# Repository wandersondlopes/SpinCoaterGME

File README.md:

# SpinCoaterGME

Nesse repositorio encontra-se todos as informações de projeto para se construir um Spin Coater Homemade. Um Spin Coater é um equipamento muito utilzado em laboratórios. Utilizando esse equipamento podemos produzir filmes de varias espessuras de acordo com o procedimento experimental. Esse equipamento foi criado no GME (Grupo de Métodos Eletroforéticos/UFG - Brasil) e sua utilização era principalmente para produção de filmes poliméricos de PDMS, PMMA e resinas. 

Esse sistema utiliza um sistema embarcado com firmware que tem código escrito em C++ e um aplicativo para dispositivos Android que possuam bluetooth. Foi entendido que era necessario muita praticidade e facilidade no manuseio das amostras. Então concebemos um dispositivo de fácil utilização via bluetooth. Com isso podemos facilitar o procedimento experimental e aumentar a produtividade nesse dispositivo.

# Aplicativo

O aplicativo mobile foi desenvolvido na plataforma Mit App Inventor e utiliza a comunicação via bluetooth para troca de dados. A interface do aplicativo tem as configurações disponiveis para realizar o procedimento experimental. O usuário pode escrever a intensidade de rotação e o tempo de rotação em segundos. Foi concebida também uma tela de login para que o usuário possa conectar seu dispositivo e configurar a senha de acesso ao aplicativo.

# Senhas de acesso

Existem duas senhas padrão a serem configuradas para o funcionamento spin coater.
A senha do aplicativo mobile e módulo HC-06. Atualmente a maneira de acessar o aplicativo com um usuário tem as seguintes etapas: precione "Entrar" com toque longo, apos aparecer a notificação para entrar como administrador confirme "Sim". A senha do módulo HC-06 é configurada por padrão "1234" e é utilizada para conectar o celular ao módulo.

# SpinCoaterV3 AT-AU - Sistema Embarcado

O Sistema Embarcado do Spin Coater foi feito utilizando Eagle, está também disponível um pdf com o fotolito para confecção da PCB. Nesse diretório encontra-se todos os arquivos para a confecção do hardware do spin coater. Foram deixadas disponíveis os terminais responsáveis dedicados para a gravação do código em hexadecimal (.hex) no microcontrolador ATmega328au.

Video de demontração:
https://youtu.be/IxnT_PpbAdY

# Firmware

O firmware foi escrito em liguagem C++ para Arduino. Para que se possa controlar a velocidade de rotação do motor determinamos o duty cicle do sinal fornecido ao driver do motor. Dessa maneira conseguimos determinar o fornecimento de corrente para o motor e sua velocidade. Como o microcontrolador opera como um oscilador nessa etapa utilizamos o dispositivo mobile para servir como timer e determinar o tempo do procedimento de rotação.

O Sistema desenvolvido é OpenSource.

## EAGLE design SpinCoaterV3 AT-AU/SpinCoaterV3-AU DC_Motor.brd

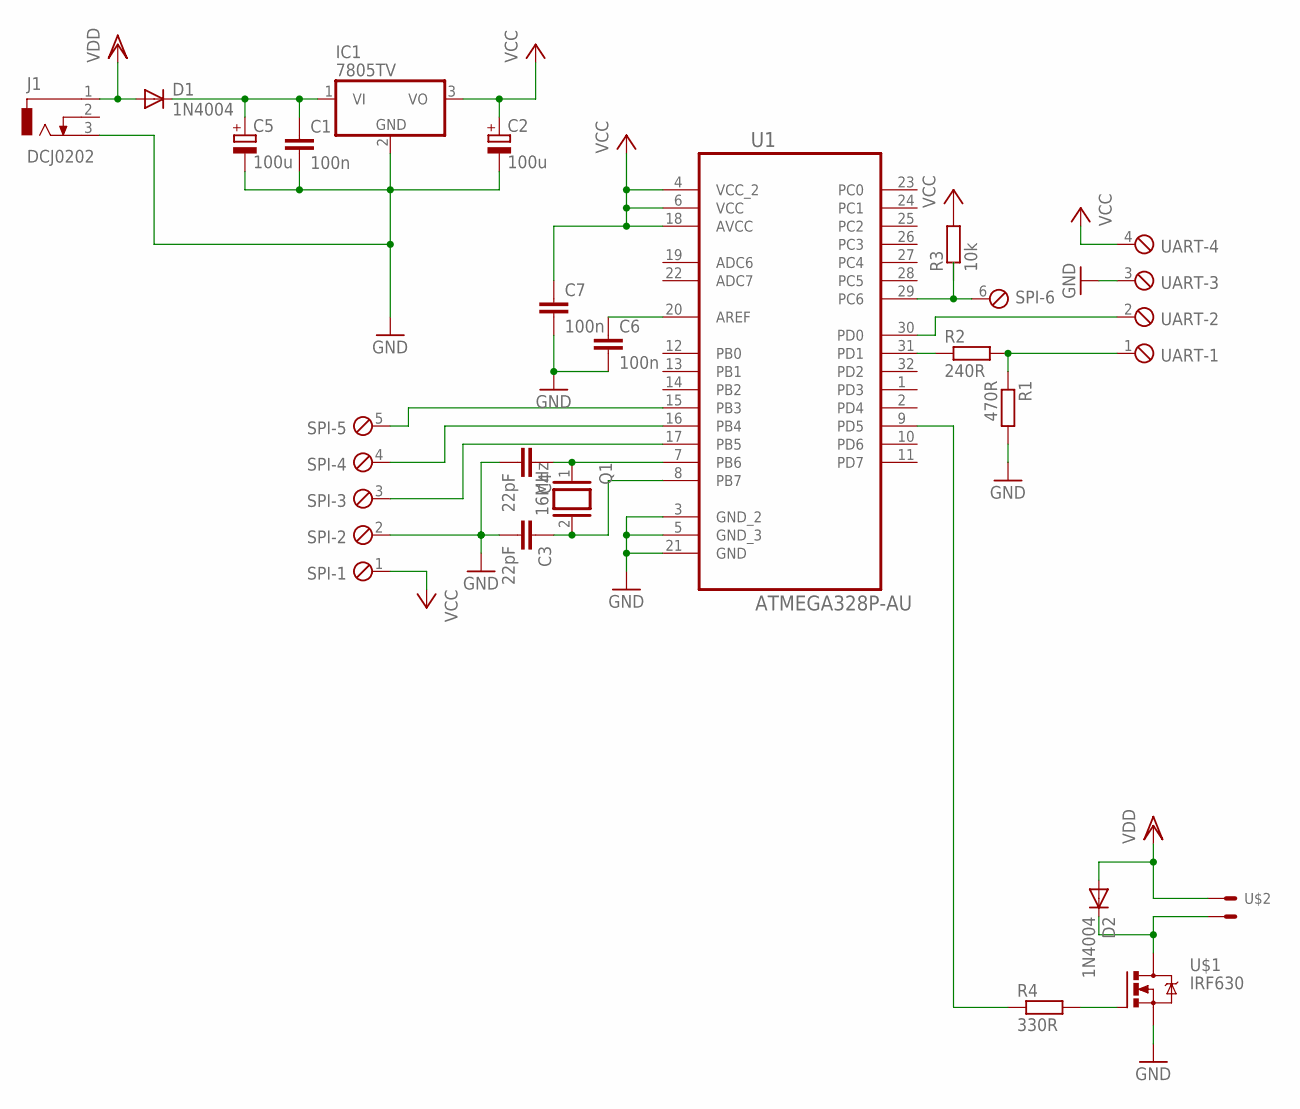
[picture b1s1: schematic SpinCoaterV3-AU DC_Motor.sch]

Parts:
C1, C6, C7: 100n; C075-032X103
C2, C5: 100u; E2,5-6
C3, C4: 22pF; C050-030X075
D1, D2: 1N4004; DO41-10
IC1: 7805TV; TO220V
J1: DCJ0202
Q1: 16MHz; QS
R1: 470R; 0207/10
R2: 240R; 0207/10
R3: 10k; 0207/10
R4: 330R; 0207/10
SPI: MPT6; 6POL254
U1: ATMEGA328P-AU; QFP80P900X900X120-32N
U$1: IRF630; TO-220BH
U$2: CON-MOTORDC; CON-MOTOR
UART: MPT4; 4POL254

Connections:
GND: C1.2, C2.-, C3.2, C4.2, C5.-, C6.2, C7.2, IC1.2 (GND), J1.3, R1.2, SPI.2, U1.3 (GND_2), U1.5 (GND_3), U1.21 (GND), U$1.S, UART.3
unnamed: R3.1, SPI.6, U1.29 (PC6)
unnamed: C4.1, Q1.1, U1.7 (PB6)
unnamed: C3.1, Q1.2, U1.8 (PB7)
unnamed: SPI.3, U1.17 (PB5)
unnamed: R2.1, U1.31 (PD1)
unnamed: SPI.4, U1.16 (PB4)
unnamed: SPI.5, U1.15 (PB3)
unnamed: R4.2, U$1.G
unnamed: U1.30 (PD0), UART.2
unnamed: R1.1, R2.2, UART.1
unnamed: R4.1, U1.9 (PD5)
unnamed: D2.C, U$1.D, U$2.P$2 (S2)
unnamed: C6.1, U1.20 (AREF)
unnamed: C1.1, C5.+, D1.C, IC1.1 (VI)
VCC: C2.+, C7.1, IC1.3 (VO), R3.2, SPI.1, U1.4 (VCC_2), U1.6 (VCC), U1.18 (AVCC), UART.4
VDD: D1.A, D2.A, J1.1, U$2.P$1 (S1)

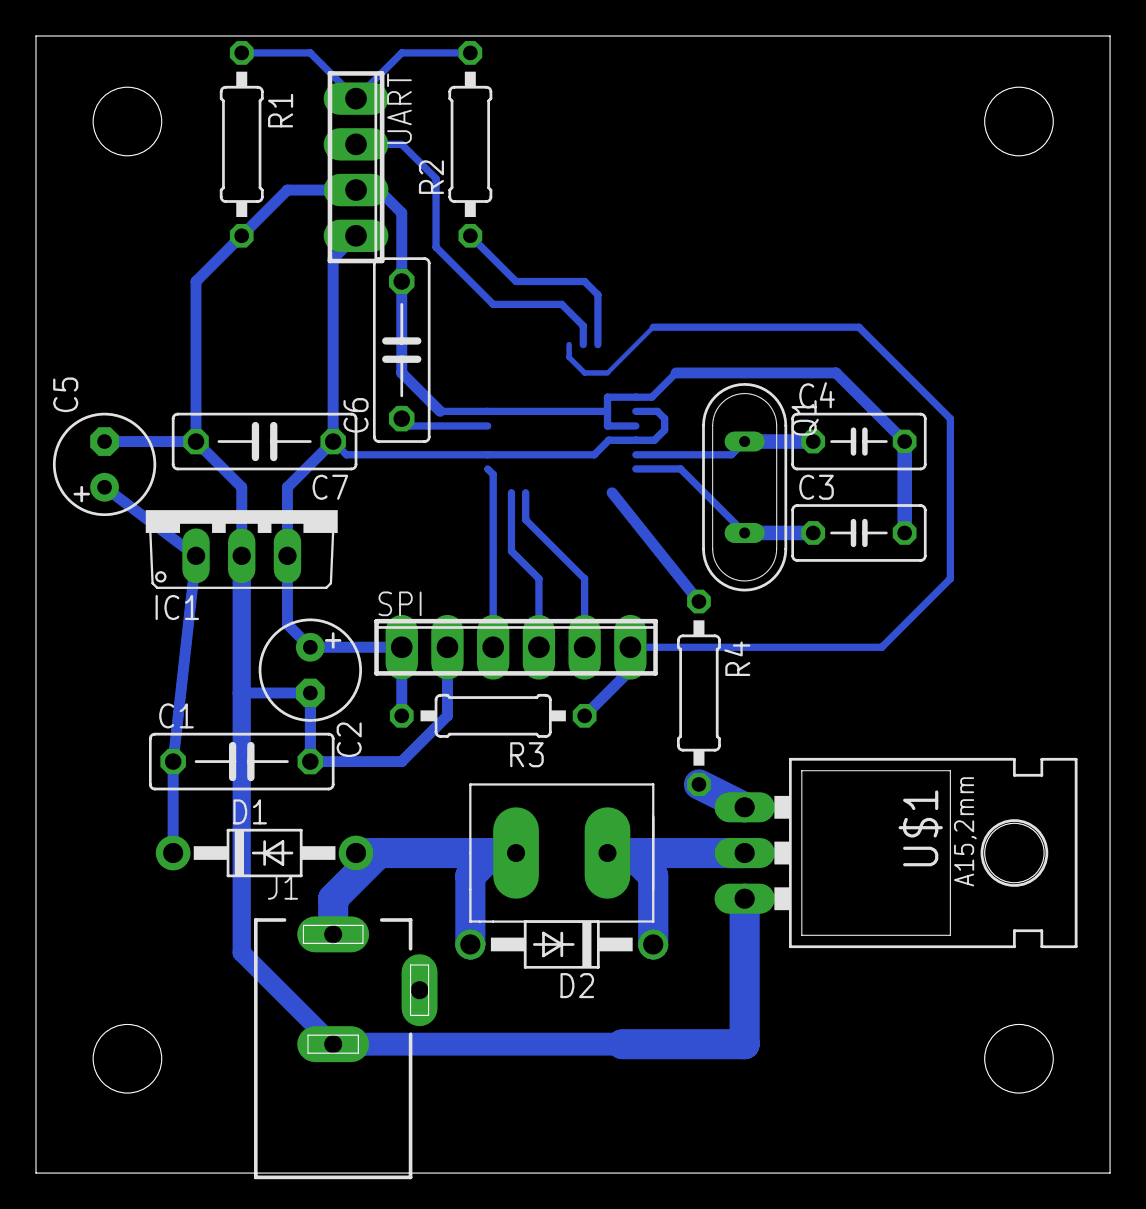
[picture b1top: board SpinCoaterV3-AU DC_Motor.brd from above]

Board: 2 copper layers, 59.7 x 63.2 mm, 21 parts (1 on the bottom side), 17 nets.

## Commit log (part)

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2020-08-19 Rename SpinCoaterV3MotorDC_Fracao_22_09_2014.ino to firmware/SpinCoaterV3MotorDC_Fracao_22_09_2014.ino
2026-01-04 Atualizar o README.md
2026-03-20 Corrigir erros de digitação e gramática no README
    Corrigido erros de digitação e gramática no README.md, incluindo ajustes na descrição do aplicativo e nas instruções de configuração.
2026-03-20 Update README with access instructions for app
    Adicionei as instruções para acessar o aplicativo com um usuário administrador.
2026-04-04 Update quote
2026-04-05 Melhorando a descrição
    Corrected description and improved clarity in the README.
2026-04-27 Publicate of MIT License to project on the repository
